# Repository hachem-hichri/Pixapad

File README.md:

# Pixapad

Pixapad is a 12-key programmable macropad designed for programmers. It provides quick access to common coding actions such as build, run, comment, copy, paste, and terminal commands, reducing repetitive keyboard shortcuts and improving workflow.

# Features

- 12 programmable keys
- Rotary encoder for scrolling and navigation
- Powered by Seeed XIAO RP2040
- KMK/QMK firmware support
- Compact desktop footprint

# Schematic 

 # PCB design 

# BOM
1x unsoldered Seeed XIAO RP2040

12x 1N4148 Diodes

12x MX-Style switches

1x  EC11 Rotary encoders

12x white blank DSA keycaps

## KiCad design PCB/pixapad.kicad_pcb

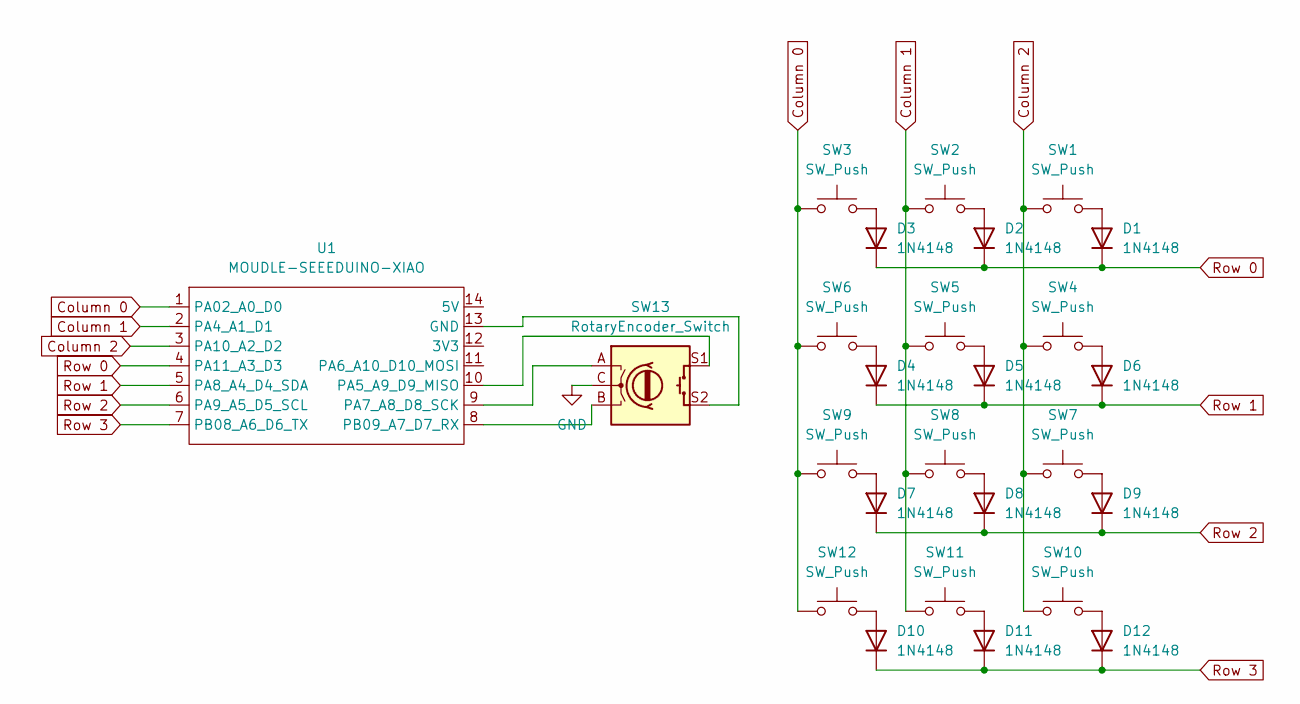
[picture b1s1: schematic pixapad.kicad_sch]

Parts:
D1, D2, D3, D4, D5, D6, D7, D8, D9, D10, D11, D12: 1N4148; D_DO-35_SOD27_P7.62mm_Horizontal
SW1, SW2, SW3, SW4, SW5, SW6, SW7, SW8, SW9, SW10, SW11, SW12: SW_Push; SW_Cherry_MX_1.00u_PCB
SW13: RotaryEncoder_Switch; RotaryEncoder_Alps_EC11E-Switch_Vertical_H20mm
U1: MOUDLE-SEEEDUINO-XIAO; XIAO-Generic-Hybrid-14P-2.54-21X17.8MM

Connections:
Column 0: SW3.1, SW6.1, SW9.1, SW12.1, U1.1 (PA02_A0_D0)
Column 1: SW2.1, SW5.1, SW8.1, SW11.1, U1.2 (PA4_A1_D1)
Column 2: SW1.1, SW4.1, SW7.1, SW10.1, U1.3 (PA10_A2_D2)
GND: SW13.C
unnamed: D1.2 (A), SW1.2
unnamed: D2.2 (A), SW2.2
unnamed: D3.2 (A), SW3.2
unnamed: D4.2 (A), SW6.2
unnamed: D5.2 (A), SW5.2
unnamed: D6.2 (A), SW4.2
unnamed: D7.2 (A), SW9.2
unnamed: D8.2 (A), SW8.2
unnamed: D9.2 (A), SW7.2
unnamed: D10.2 (A), SW12.2
unnamed: D11.2 (A), SW11.2
unnamed: D12.2 (A), SW10.2
unnamed: SW13.S2, U1.13 (GND)
unnamed: SW13.S1, U1.10 (PA5_A9_D9_MISO)
unnamed: SW13.A, U1.9 (PA7_A8_D8_SCK)
unnamed: SW13.B, U1.8 (PB09_A7_D7_RX)
Row 0: D1.1 (K), D2.1 (K), D3.1 (K), U1.4 (PA11_A3_D3)
Row 1: D4.1 (K), D5.1 (K), D6.1 (K), U1.5 (PA8_A4_D4_SDA)
Row 2: D7.1 (K), D8.1 (K), D9.1 (K), U1.6 (PA9_A5_D5_SCL)
Row 3: D10.1 (K), D11.1 (K), D12.1 (K), U1.7 (PB08_A6_D6_TX)

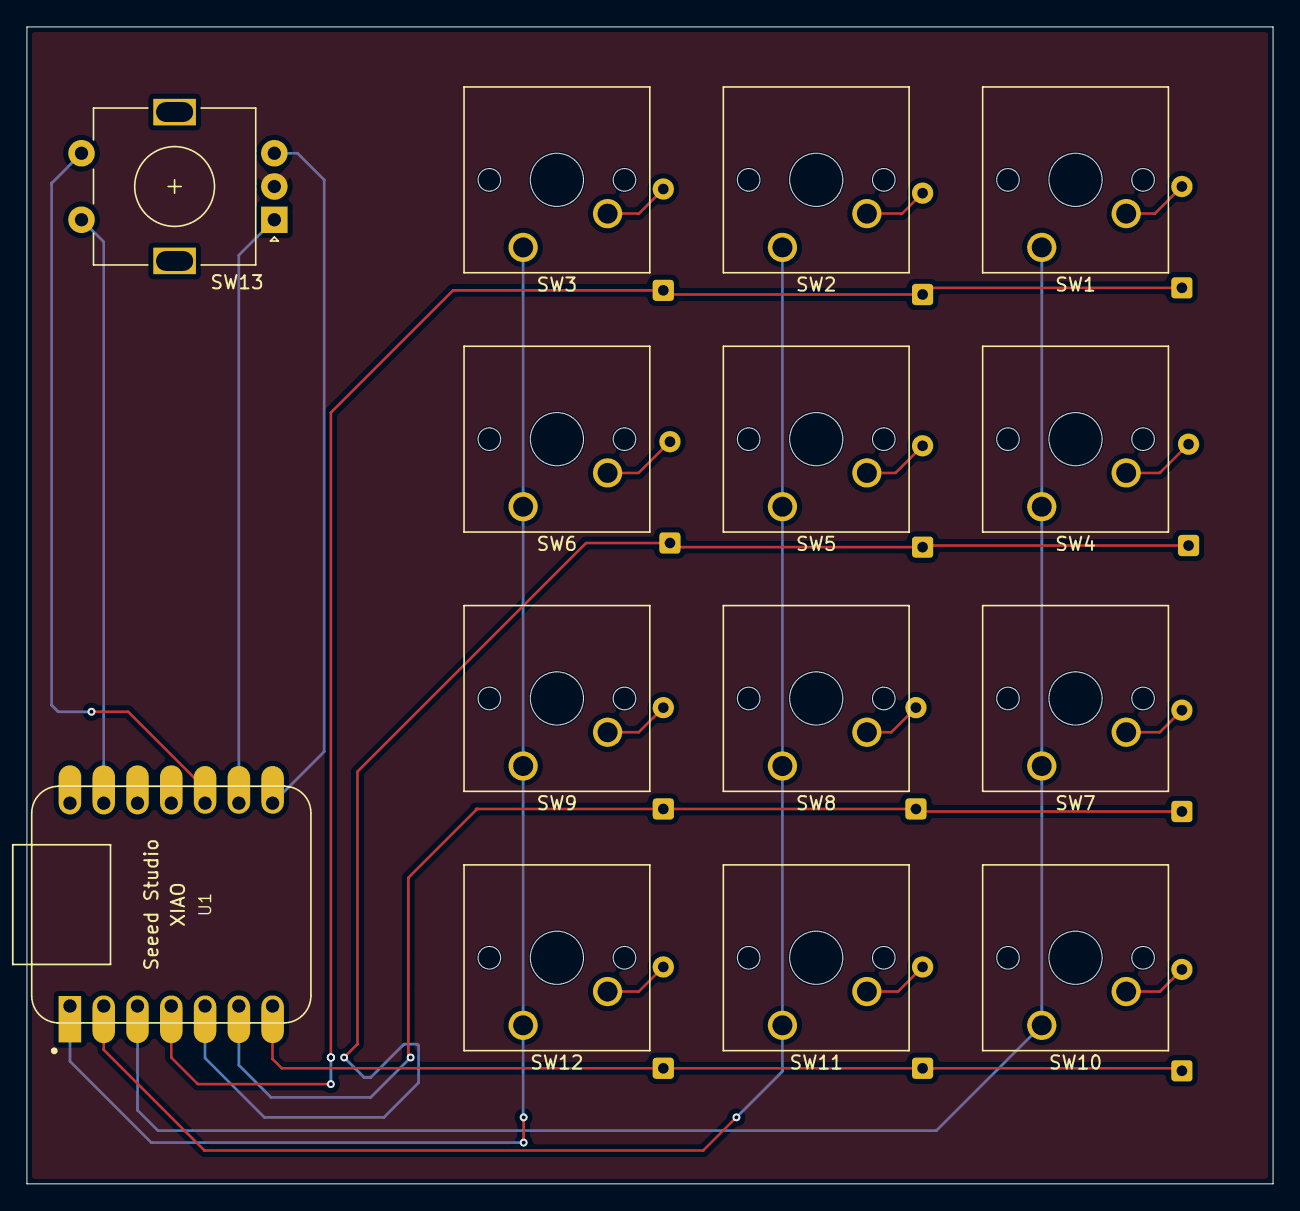
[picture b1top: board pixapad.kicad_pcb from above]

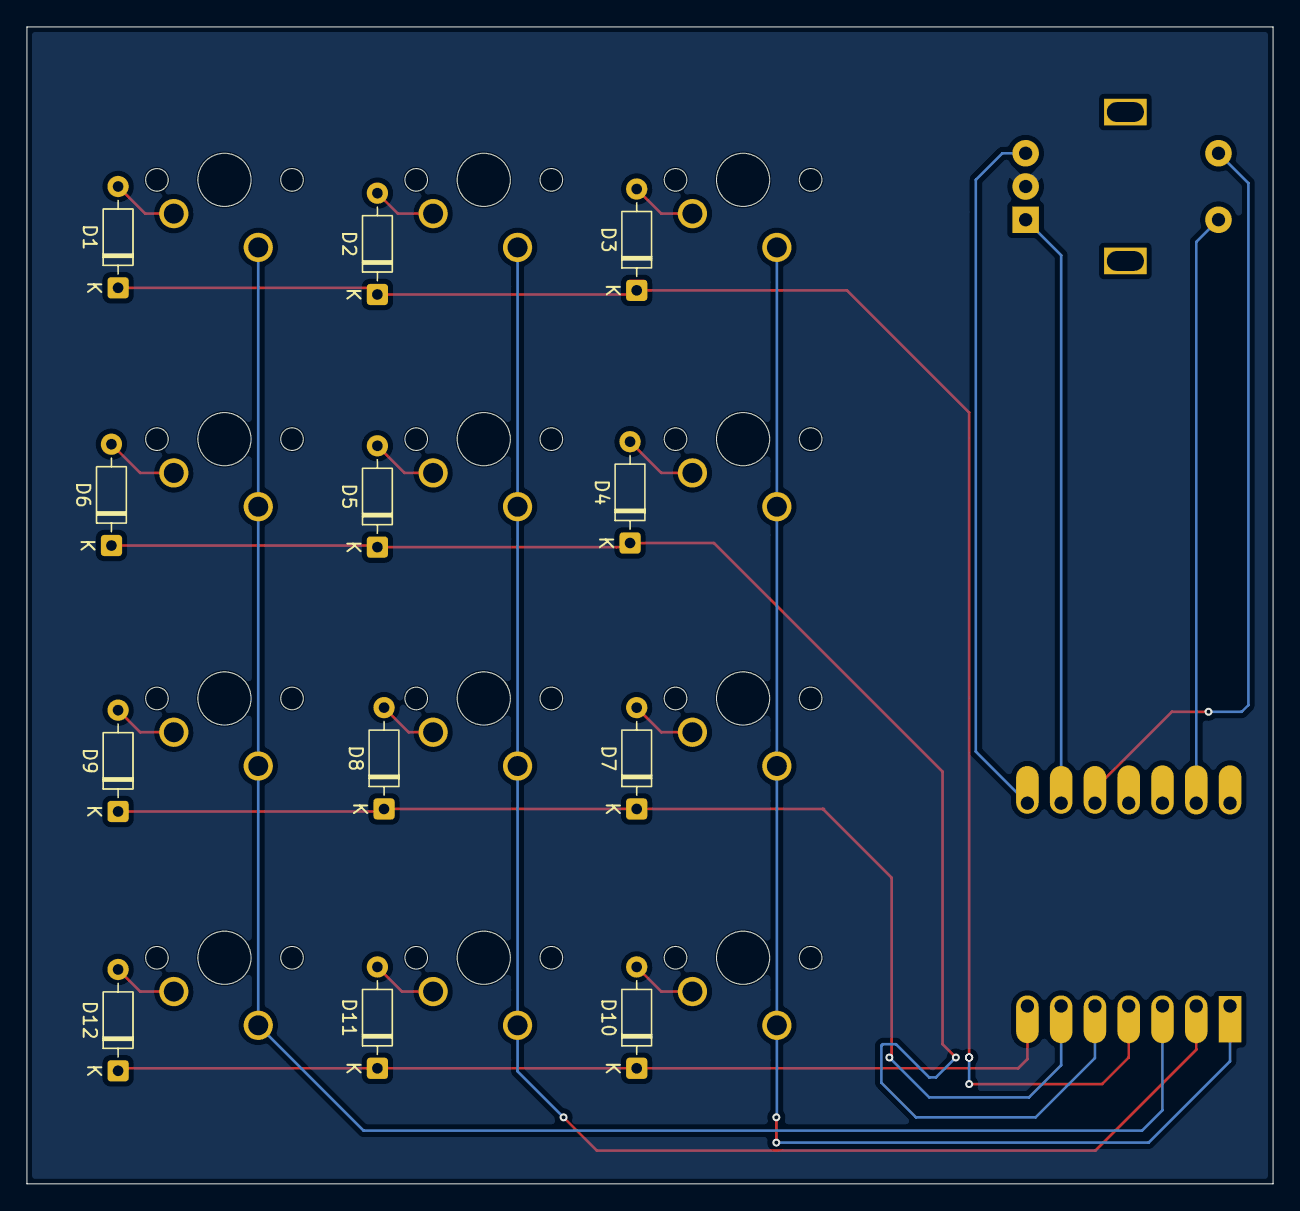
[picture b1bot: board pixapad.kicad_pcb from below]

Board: 2 copper layers, 93.7 x 87.0 mm, 26 parts (12 on the bottom side), 23 nets.

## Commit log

2026-06-21 Enhance README with schematic, PCB, and BOM details
    Added schematic, PCB design, and BOM sections to README.
2026-06-22 Update image in README.md for PCB design section
2026-06-22 Rename fp-lib-table to PCB/fp-lib-table
2026-06-22 Rename pixapad.kicad_pcb to PCB/pixapad.kicad_pcb
2026-06-22 Rename pixapad.kicad_prl to PCB/pixapad.kicad_prl
2026-06-22 Rename pixapad.kicad_pro to PCB/pixapad.kicad_pro
2026-06-22 Rename pixapad.kicad_sch to PCB/pixapad.kicad_sch
2026-06-22 Rename ~pixapad.kicad_pro.lck to PCB/~pixapad.kicad_pro.lck
2026-06-22 Enhance README with detailed description and features
    Expanded the description and added features list for clarity.
